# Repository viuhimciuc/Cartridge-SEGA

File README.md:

# 🎮 Cartridge-SEGA: Sega Genesis Cartridge PCBs 🕹️

An open-source collection of hardware design files for **Sega Genesis / Mega Drive** cartridge PCBs (Printed Circuit Boards). Designed from scratch or reverse-engineered using **KiCad**, this repository provides schemas and layouts for creating custom cartridges, multi-game boards, and memory adapters.

---

## 📂 Repository Structure

The project is organized into several key hardware modules:

*   **`GEN-CART-171-6329A-7147A`** — Replica or custom variant of standard Sega Genesis cartridge PCBs.
*   **`GEN-CART-171-6570A`** — Re-engineered files based on the classic 171-6570A board layout.
*   **`GEN-CART-171-6570A_MultiGames`** — Modded version supporting multiple games on a single cartridge via bank switching or custom routing.
*   **`TSOP_Adapter_M29FxxxF`** — A specialized adapter board converting TSOP flash memory chips (like the M29F series) to DIP/SOP layouts suitable for retro console cartridges.

---

## 🛠️ Built With

*   [KiCad EDA](https://www.kicad.org/) — A Cross-Platform and Open Source Electronics Design Automation Suite.

---

## 📸 Gallery & Visuals

### 🔧 Component Placement / PCB Layout Preview

---

## 🚀 Getting Started

### 📋 Prerequisites
To open, edit, or export production files (Gerbers) from this project, you need:
*   **KiCad 7.0 or newer** (Recommended)

### 📥 Cloning the Repository
```bash
git clone https://github.com/viuhimciuc/Cartridge-SEGA.git
```

### ⚙️ How to Generate Gerber Files for Manufacturing
1. Open the `.kicad_pro` project file from any folder in KiCad.
2. Open the **PCB Editor** (`.kicad_pcb`).
3. Go to **File** -> **Fabrication Outputs** -> **Gerbers (.gbr)**.
4. Set your output directory and click **Plot**.
5. Click **Generate Drill Files** to export standard NC drill configurations.
6. Zip all generated files and send them to your preferred PCB manufacturer (e.g., JLCPCB, PCBWay).

---

## 🤝 Contributing

Contributions, bug reports, and hardware improvements are highly welcome! 
1. **Fork** the Project.
2. Create your **Feature Branch** (`git checkout -b feature/AmazingFeature`).
3. **Commit** your Changes (`git commit -m 'Add some AmazingFeature'`).
4. **Push** to the Branch (`git push origin feature/AmazingFeature`).
5. Open a **Pull Request**.

---

## 📄 License

This project is licensed under the MIT License - see the [LICENSE](LICENSE) file for details.

---

<p align="center"> Developed with ❤️ for the Retro Gaming Community </p>

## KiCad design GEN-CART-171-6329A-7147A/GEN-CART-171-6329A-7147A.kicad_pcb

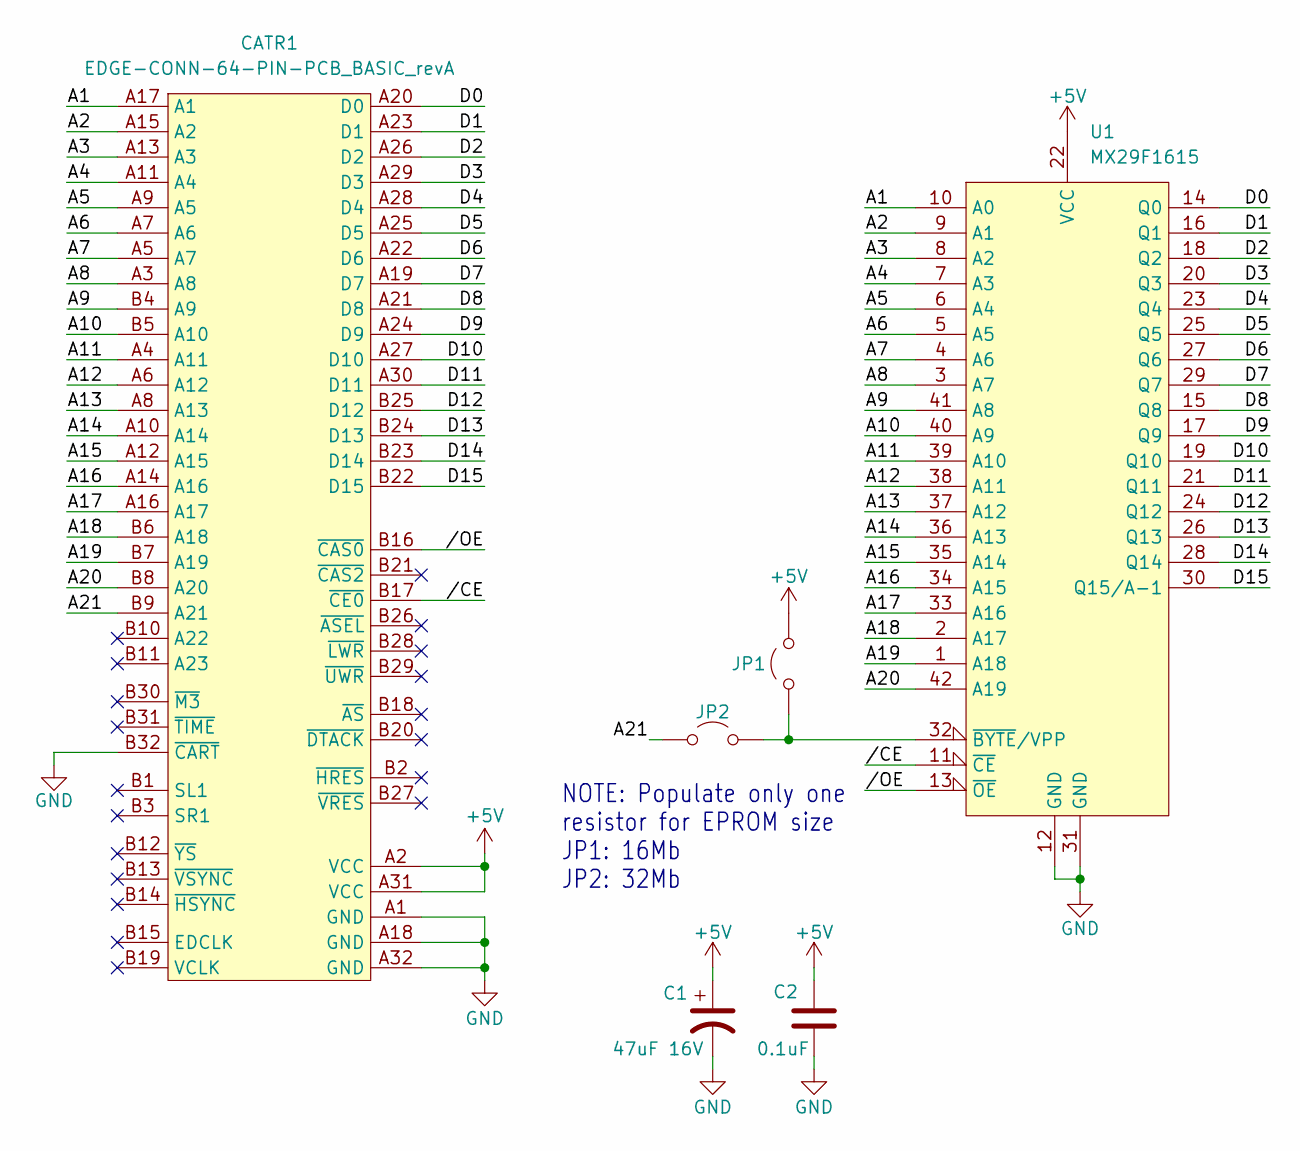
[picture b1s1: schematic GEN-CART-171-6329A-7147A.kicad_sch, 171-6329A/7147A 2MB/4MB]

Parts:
C1: 47uF 16V; CP_Radial_D5.0mm_P2.50mm
C2: 0.1uF; C_Axial_L3.8mm_D2.6mm_P10.00mm_Horizontal
CATR1: EDGE-CONN-64-PIN-PCB_BASIC_revA; PCB_revA-CART-64-2.54-CONN
JP1, JP2: Jumper_2_Open; Jumper_P10.16mm_D0.7mm
U1: MX29F1615; DIP-42_W15.24mm

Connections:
+5V: C1.1, C2.1, CATR1.A2 (VCC), CATR1.A31 (VCC), JP1.2 (B), U1.22 (VCC)
/A1: CATR1.A17 (A1), U1.10 (A0)
/A2: CATR1.A15 (A2), U1.9 (A1)
/A3: CATR1.A13 (A3), U1.8 (A2)
/A4: CATR1.A11 (A4), U1.7 (A3)
/A5: CATR1.A9 (A5), U1.6 (A4)
/A6: CATR1.A7 (A6), U1.5 (A5)
/A7: CATR1.A5 (A7), U1.4 (A6)
/A8: CATR1.A3 (A8), U1.3 (A7)
/A9: CATR1.B4 (A9), U1.41 (A8)
/A10: CATR1.B5 (A10), U1.40 (A9)
/A11: CATR1.A4 (A11), U1.39 (A10)
/A12: CATR1.A6 (A12), U1.38 (A11)
/A13: CATR1.A8 (A13), U1.37 (A12)
/A14: CATR1.A10 (A14), U1.36 (A13)
/A15: CATR1.A12 (A15), U1.35 (A14)
/A16: CATR1.A14 (A16), U1.34 (A15)
/A17: CATR1.A16 (A17), U1.33 (A16)
/A18: CATR1.B6 (A18), U1.2 (A17)
/A19: CATR1.B7 (A19), U1.1 (A18)
/A20: CATR1.B8 (A20), U1.42 (A19)
/A21: CATR1.B9 (A21), JP2.1 (A)
/D0: CATR1.A20 (D0), U1.14 (Q0)
/D1: CATR1.A23 (D1), U1.16 (Q1)
/D2: CATR1.A26 (D2), U1.18 (Q2)
/D3: CATR1.A29 (D3), U1.20 (Q3)
/D4: CATR1.A28 (D4), U1.23 (Q4)
/D5: CATR1.A25 (D5), U1.25 (Q5)
/D6: CATR1.A22 (D6), U1.27 (Q6)
/D7: CATR1.A19 (D7), U1.29 (Q7)
/D8: CATR1.A21 (D8), U1.15 (Q8)
/D9: CATR1.A24 (D9), U1.17 (Q9)
/D10: CATR1.A27 (D10), U1.19 (Q10)
/D11: CATR1.A30 (D11), U1.21 (Q11)
/D12: CATR1.B25 (D12), U1.24 (Q12)
/D13: CATR1.B24 (D13), U1.26 (Q13)
/D14: CATR1.B23 (D14), U1.28 (Q14)
/D15: CATR1.B22 (D15), U1.30 (Q15/A-1)
//CE: CATR1.B17 (~CE0), U1.11 (~CE)
//OE: CATR1.B16 (~CAS0), U1.13 (~OE)
GND: C1.2, C2.2, CATR1.A1 (GND), CATR1.A18 (GND), CATR1.A32 (GND), CATR1.B32 (~CART), U1.12 (GND), U1.31 (GND)
unnamed: JP1.1 (A), JP2.2 (B), U1.32 (~BYTE/VPP)

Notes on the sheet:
NOTE: Populate only one resistor for EPROM size JP1: 16Mb JP2: 32Mb

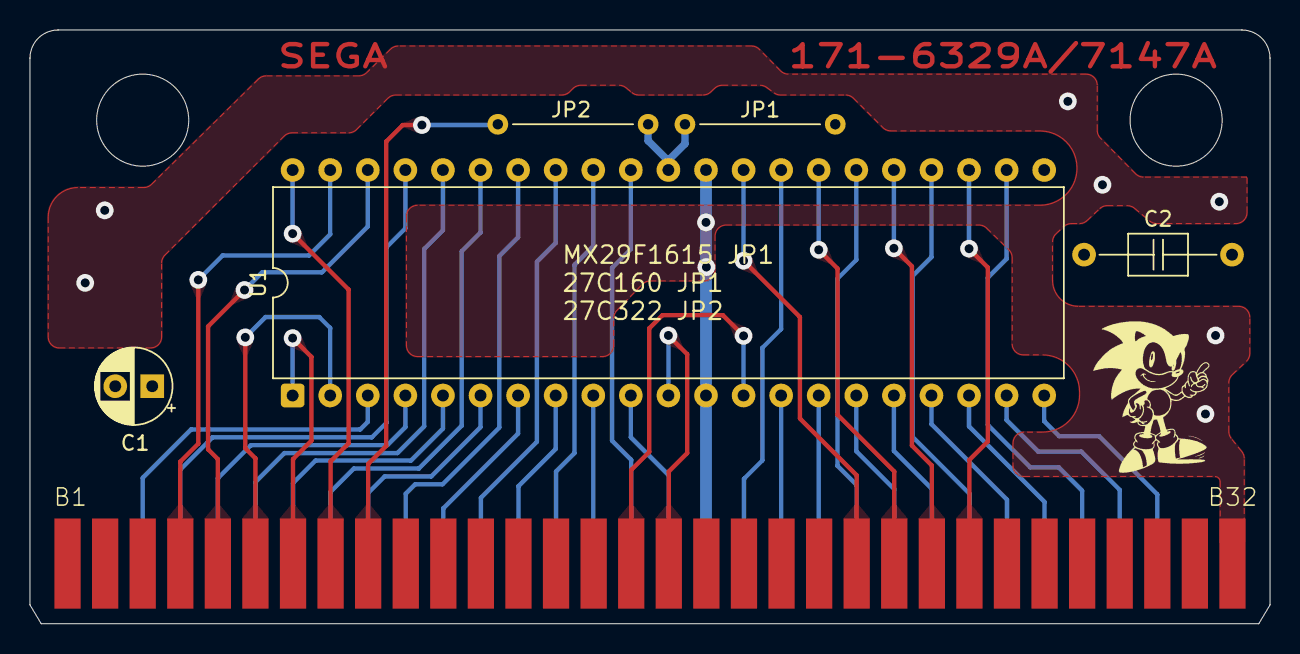
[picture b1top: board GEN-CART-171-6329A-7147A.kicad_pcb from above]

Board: 2 copper layers, 83.8 x 40.1 mm, 6 parts (0 on the bottom side), 42 nets.

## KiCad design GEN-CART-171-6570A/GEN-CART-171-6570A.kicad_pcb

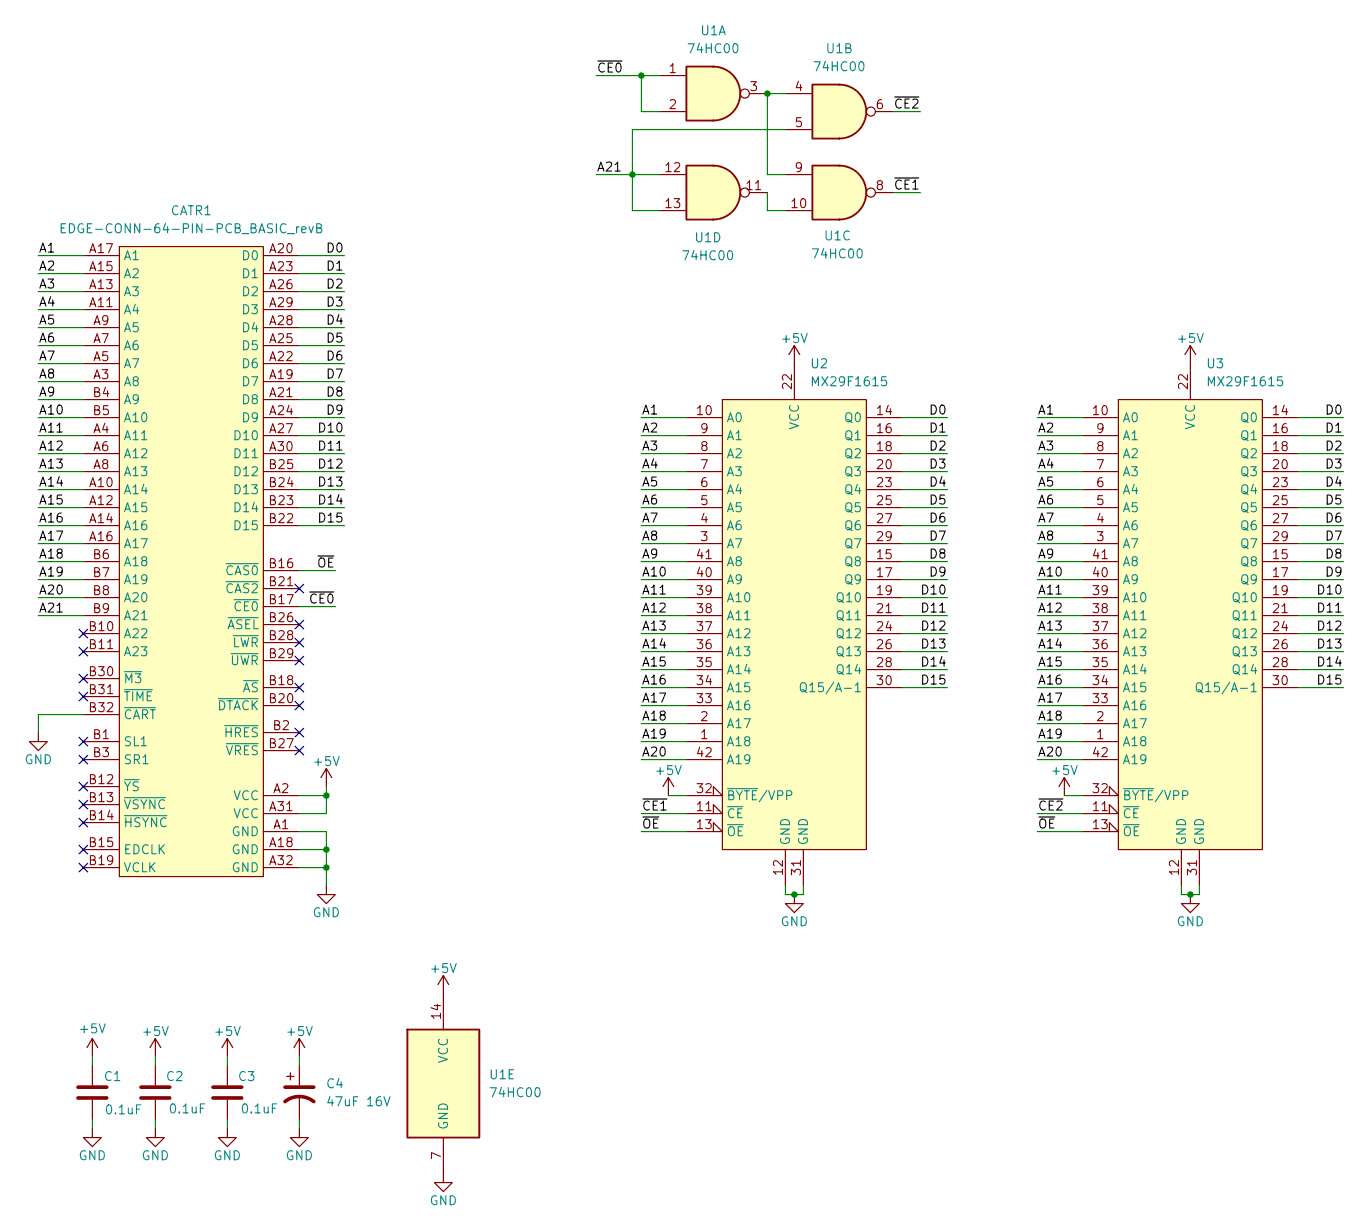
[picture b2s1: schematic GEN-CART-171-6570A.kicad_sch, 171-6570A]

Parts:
C1, C2, C3: 0.1uF; C_Axial_L3.8mm_D2.6mm_P10.00mm_Horizontal
C4: 47uF 16V; CP_Radial_D5.0mm_P2.50mm
CATR1: EDGE-CONN-64-PIN-PCB_BASIC_revB; PCB_revB-CART-64-2.54-CONN
U1: 74HC00; DIP-14_W7.62mm
U2, U3: MX29F1615; DIP-42_W15.24mm

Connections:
+5V: C1.1, C2.1, C3.1, C4.1, CATR1.A2 (VCC), CATR1.A31 (VCC), U1.14 (VCC), U2.22 (VCC), U2.32 (~BYTE/VPP), U3.22 (VCC), U3.32 (~BYTE/VPP)
/A1: CATR1.A17 (A1), U2.10 (A0), U3.10 (A0)
/A2: CATR1.A15 (A2), U2.9 (A1), U3.9 (A1)
/A3: CATR1.A13 (A3), U2.8 (A2), U3.8 (A2)
/A4: CATR1.A11 (A4), U2.7 (A3), U3.7 (A3)
/A5: CATR1.A9 (A5), U2.6 (A4), U3.6 (A4)
/A6: CATR1.A7 (A6), U2.5 (A5), U3.5 (A5)
/A7: CATR1.A5 (A7), U2.4 (A6), U3.4 (A6)
/A8: CATR1.A3 (A8), U2.3 (A7), U3.3 (A7)
/A9: CATR1.B4 (A9), U2.41 (A8), U3.41 (A8)
/A10: CATR1.B5 (A10), U2.40 (A9), U3.40 (A9)
/A11: CATR1.A4 (A11), U2.39 (A10), U3.39 (A10)
/A12: CATR1.A6 (A12), U2.38 (A11), U3.38 (A11)
/A13: CATR1.A8 (A13), U2.37 (A12), U3.37 (A12)
/A14: CATR1.A10 (A14), U2.36 (A13), U3.36 (A13)
/A15: CATR1.A12 (A15), U2.35 (A14), U3.35 (A14)
/A16: CATR1.A14 (A16), U2.34 (A15), U3.34 (A15)
/A17: CATR1.A16 (A17), U2.33 (A16), U3.33 (A16)
/A18: CATR1.B6 (A18), U2.2 (A17), U3.2 (A17)
/A19: CATR1.B7 (A19), U2.1 (A18), U3.1 (A18)
/A20: CATR1.B8 (A20), U2.42 (A19), U3.42 (A19)
/A21: CATR1.B9 (A21), U1.5, U1.12, U1.13
/D0: CATR1.A20 (D0), U2.14 (Q0), U3.14 (Q0)
/D1: CATR1.A23 (D1), U2.16 (Q1), U3.16 (Q1)
/D2: CATR1.A26 (D2), U2.18 (Q2), U3.18 (Q2)
/D3: CATR1.A29 (D3), U2.20 (Q3), U3.20 (Q3)
/D4: CATR1.A28 (D4), U2.23 (Q4), U3.23 (Q4)
/D5: CATR1.A25 (D5), U2.25 (Q5), U3.25 (Q5)
/D6: CATR1.A22 (D6), U2.27 (Q6), U3.27 (Q6)
/D7: CATR1.A19 (D7), U2.29 (Q7), U3.29 (Q7)
/D8: CATR1.A21 (D8), U2.15 (Q8), U3.15 (Q8)
/D9: CATR1.A24 (D9), U2.17 (Q9), U3.17 (Q9)
/D10: CATR1.A27 (D10), U2.19 (Q10), U3.19 (Q10)
/D11: CATR1.A30 (D11), U2.21 (Q11), U3.21 (Q11)
/D12: CATR1.B25 (D12), U2.24 (Q12), U3.24 (Q12)
/D13: CATR1.B24 (D13), U2.26 (Q13), U3.26 (Q13)
/D14: CATR1.B23 (D14), U2.28 (Q14), U3.28 (Q14)
/D15: CATR1.B22 (D15), U2.30 (Q15/A-1), U3.30 (Q15/A-1)
/~CE0: CATR1.B17 (~CE0), U1.1, U1.2
/~CE1: U1.8, U2.11 (~CE)
/~CE2: U1.6, U3.11 (~CE)
/~OE: CATR1.B16 (~CAS0), U2.13 (~OE), U3.13 (~OE)
GND: C1.2, C2.2, C3.2, C4.2, CATR1.A1 (GND), CATR1.A18 (GND), CATR1.A32 (GND), CATR1.B32 (~CART), U1.7 (GND), U2.12 (GND), U2.31 (GND), U3.12 (GND), U3.31 (GND); also elsewhere on the board
unnamed: U1.3, U1.4, U1.9
unnamed: U1.10, U1.11

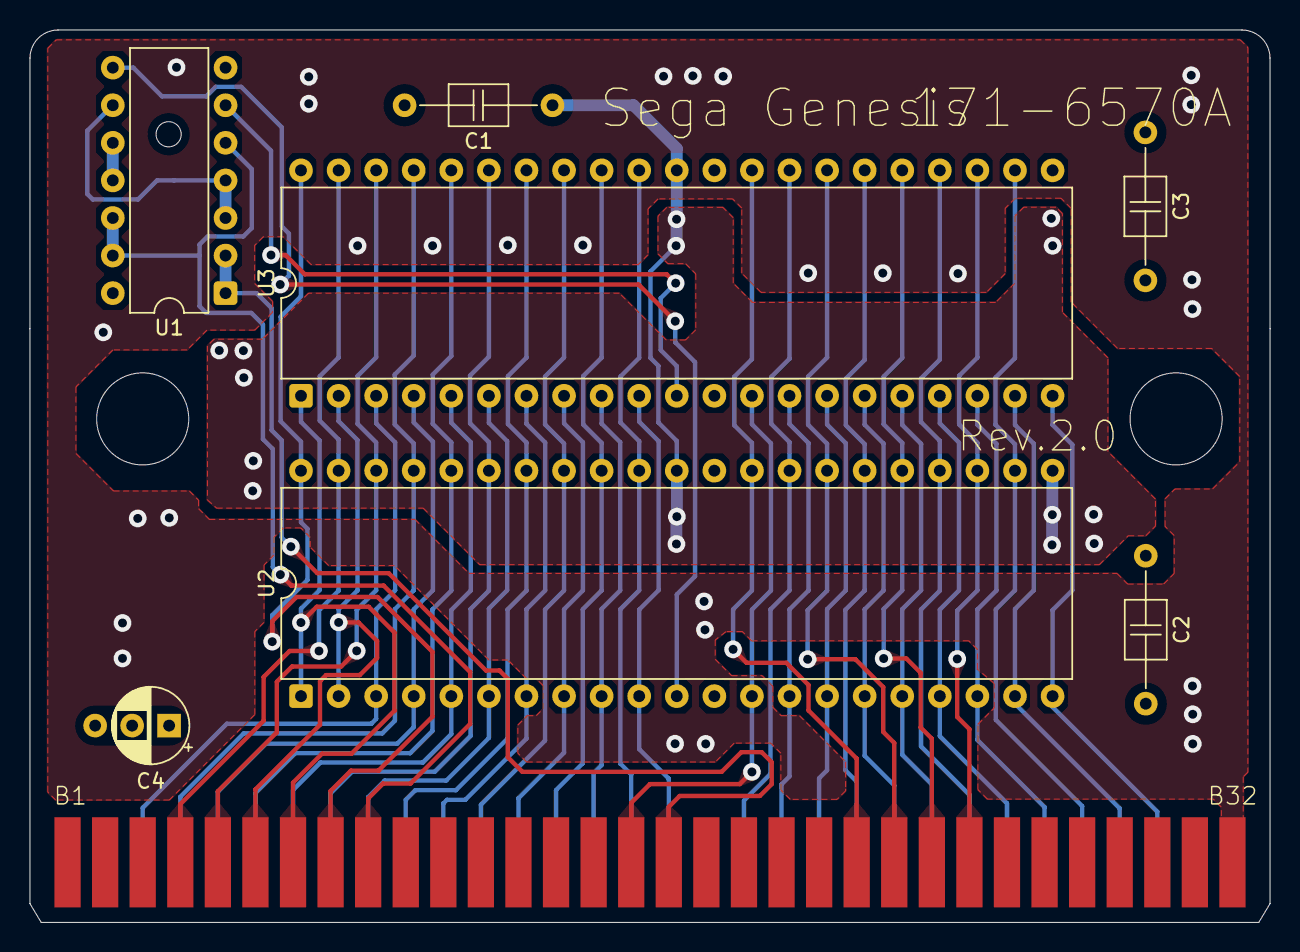
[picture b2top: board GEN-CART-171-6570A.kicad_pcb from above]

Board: 2 copper layers, 83.8 x 60.3 mm, 9 parts (0 on the bottom side), 45 nets.

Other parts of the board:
GND: (no value)

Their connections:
GND: GND.2; also elsewhere on the board

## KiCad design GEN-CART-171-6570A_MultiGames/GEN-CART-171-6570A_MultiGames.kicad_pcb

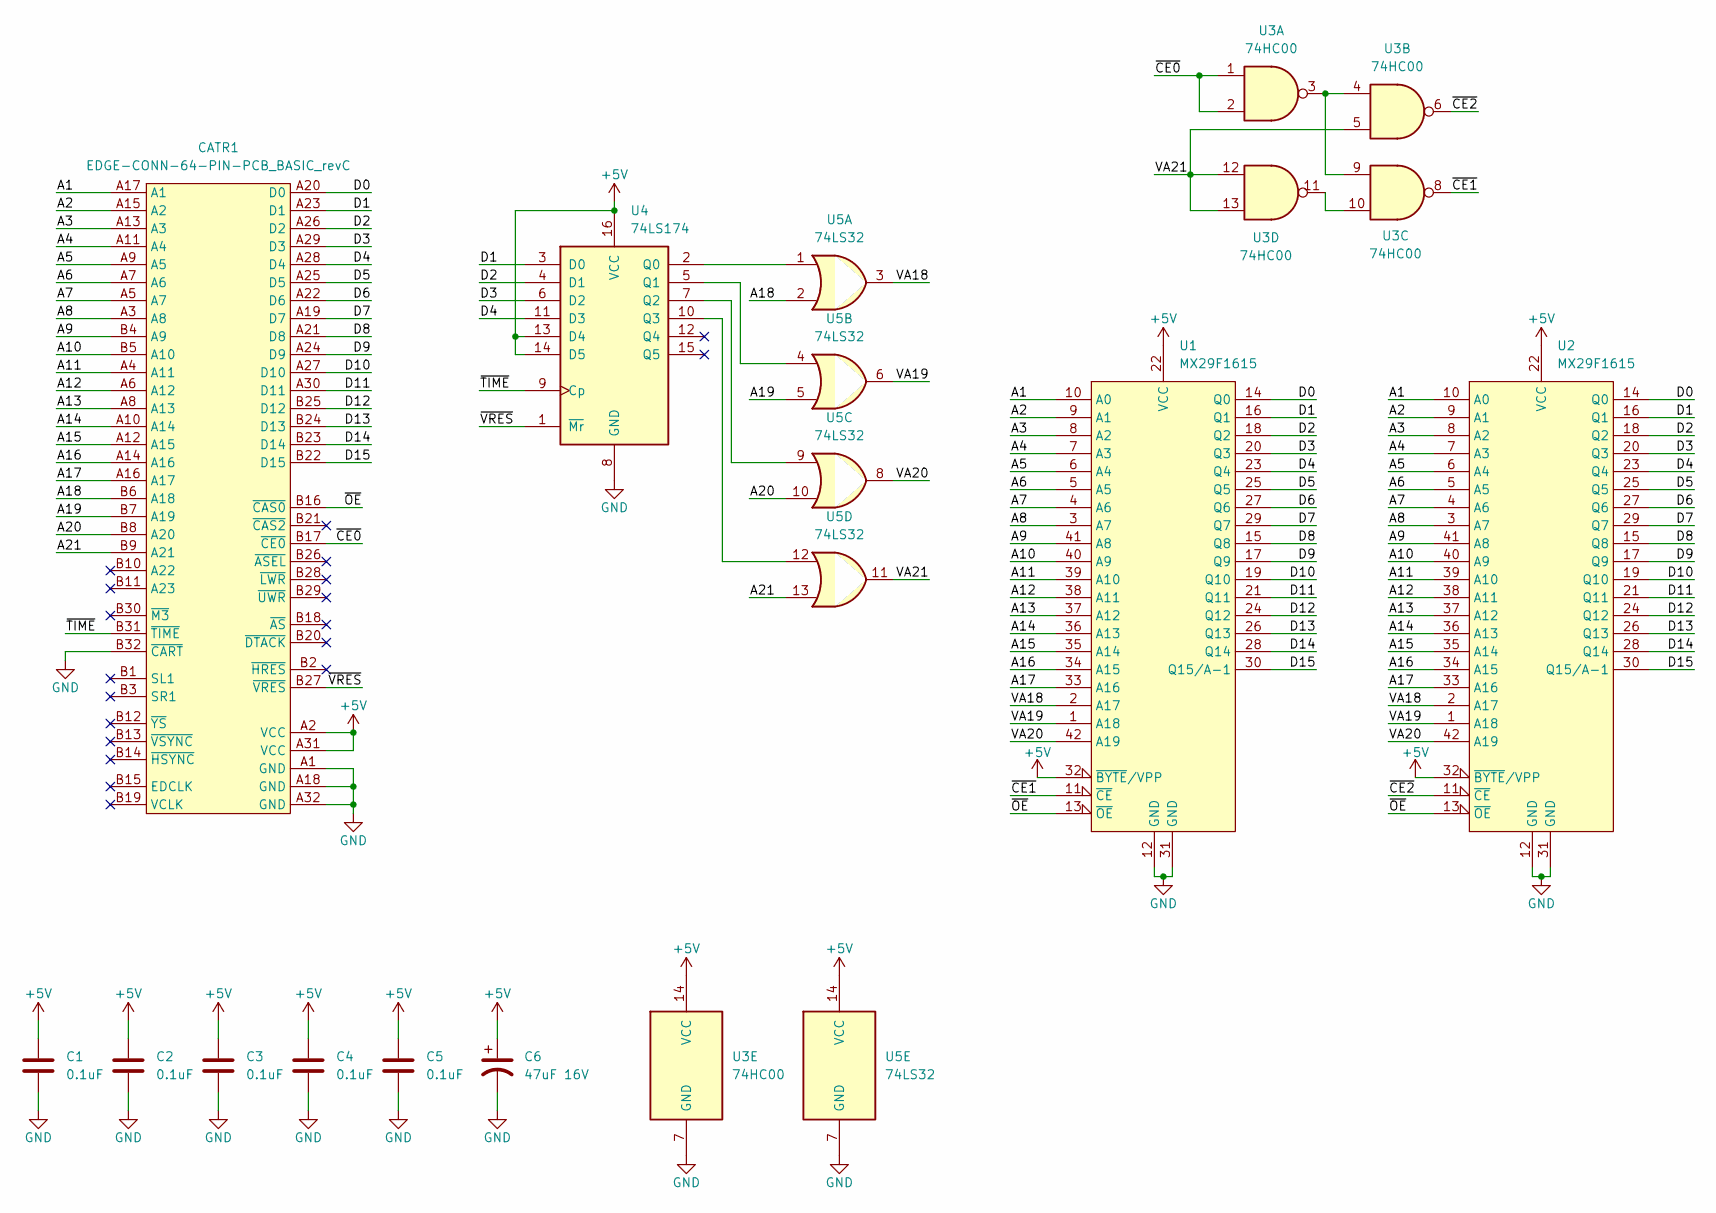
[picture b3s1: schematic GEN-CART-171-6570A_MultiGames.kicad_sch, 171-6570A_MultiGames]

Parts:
C1: 0.1uF; C_Axial_L3.8mm_D2.6mm_P12.50mm_Horizontal
C2, C3: 0.1uF; C_Axial_L3.8mm_D2.6mm_P10.00mm_Horizontal
C4, C5: 0.1uF; C_0805_2012Metric_Pad1.18x1.45mm_HandSolder
C6: 47uF 16V; CP_Radial_D5.0mm_P2.50mm
CATR1: EDGE-CONN-64-PIN-PCB_BASIC_revC; PCB_revC-CART-64-2.54-CONN
U1, U2: MX29F1615; DIP-42_W15.24mm
U3: 74HC00; DIP-14_W7.62mm
U4: 74LS174; SOIC-16_3.9x9.9mm_P1.27mm
U5: 74LS32; SOIC-14_3.9x8.7mm_P1.27mm

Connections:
+5V: C1.1, C2.1, C3.1, C4.1, C5.1, C6.1, CATR1.A2 (VCC), CATR1.A31 (VCC), U1.22 (VCC), U1.32 (~BYTE/VPP), U2.22 (VCC), U2.32 (~BYTE/VPP), U3.14 (VCC), U4.13 (D4), U4.14 (D5), U4.16 (VCC), U5.14 (VCC)
/A1: CATR1.A17 (A1), U1.10 (A0), U2.10 (A0)
/A2: CATR1.A15 (A2), U1.9 (A1), U2.9 (A1)
/A3: CATR1.A13 (A3), U1.8 (A2), U2.8 (A2)
/A4: CATR1.A11 (A4), U1.7 (A3), U2.7 (A3)
/A5: CATR1.A9 (A5), U1.6 (A4), U2.6 (A4)
/A6: CATR1.A7 (A6), U1.5 (A5), U2.5 (A5)
/A7: CATR1.A5 (A7), U1.4 (A6), U2.4 (A6)
/A8: CATR1.A3 (A8), U1.3 (A7), U2.3 (A7)
/A9: CATR1.B4 (A9), U1.41 (A8), U2.41 (A8)
/A10: CATR1.B5 (A10), U1.40 (A9), U2.40 (A9)
/A11: CATR1.A4 (A11), U1.39 (A10), U2.39 (A10)
/A12: CATR1.A6 (A12), U1.38 (A11), U2.38 (A11)
/A13: CATR1.A8 (A13), U1.37 (A12), U2.37 (A12)
/A14: CATR1.A10 (A14), U1.36 (A13), U2.36 (A13)
/A15: CATR1.A12 (A15), U1.35 (A14), U2.35 (A14)
/A16: CATR1.A14 (A16), U1.34 (A15), U2.34 (A15)
/A17: CATR1.A16 (A17), U1.33 (A16), U2.33 (A16)
/A18: CATR1.B6 (A18), U5.2
/A19: CATR1.B7 (A19), U5.5
/A20: CATR1.B8 (A20), U5.10
/A21: CATR1.B9 (A21), U5.13
/D0: CATR1.A20 (D0), U1.14 (Q0), U2.14 (Q0)
/D1: CATR1.A23 (D1), U1.16 (Q1), U2.16 (Q1), U4.3 (D0)
/D2: CATR1.A26 (D2), U1.18 (Q2), U2.18 (Q2), U4.4 (D1)
/D3: CATR1.A29 (D3), U1.20 (Q3), U2.20 (Q3), U4.6 (D2)
/D4: CATR1.A28 (D4), U1.23 (Q4), U2.23 (Q4), U4.11 (D3)
/D5: CATR1.A25 (D5), U1.25 (Q5), U2.25 (Q5)
/D6: CATR1.A22 (D6), U1.27 (Q6), U2.27 (Q6)
/D7: CATR1.A19 (D7), U1.29 (Q7), U2.29 (Q7)
/D8: CATR1.A21 (D8), U1.15 (Q8), U2.15 (Q8)
/D9: CATR1.A24 (D9), U1.17 (Q9), U2.17 (Q9)
/D10: CATR1.A27 (D10), U1.19 (Q10), U2.19 (Q10)
/D11: CATR1.A30 (D11), U1.21 (Q11), U2.21 (Q11)
/D12: CATR1.B25 (D12), U1.24 (Q12), U2.24 (Q12)
/D13: CATR1.B24 (D13), U1.26 (Q13), U2.26 (Q13)
/D14: CATR1.B23 (D14), U1.28 (Q14), U2.28 (Q14)
/D15: CATR1.B22 (D15), U1.30 (Q15/A-1), U2.30 (Q15/A-1)
/VA18: U1.2 (A17), U2.2 (A17), U5.3
/VA19: U1.1 (A18), U2.1 (A18), U5.6
/VA20: U1.42 (A19), U2.42 (A19), U5.8
/VA21: U3.5, U3.12, U3.13, U5.11
/~CE0: CATR1.B17 (~CE0), U3.1, U3.2
/~CE1: U1.11 (~CE), U3.8
/~CE2: U2.11 (~CE), U3.6
/~OE: CATR1.B16 (~CAS0), U1.13 (~OE), U2.13 (~OE)
/~TIME: CATR1.B31 (~TIME), U4.9 (Cp)
/~VRES: CATR1.B27 (~VRES), U4.1 (~Mr)
GND: C1.2, C2.2, C3.2, C4.2, C5.2, C6.2, CATR1.A1 (GND), CATR1.A18 (GND), CATR1.A32 (GND), CATR1.B32 (~CART), U1.12 (GND), U1.31 (GND), U2.12 (GND), U2.31 (GND), U3.7 (GND), U4.8 (GND), U5.7 (GND)
unnamed: U3.3, U3.4, U3.9
unnamed: U3.10, U3.11
unnamed: U4.2 (Q0), U5.1
unnamed: U4.5 (Q1), U5.4
unnamed: U4.7 (Q2), U5.9
unnamed: U4.10 (Q3), U5.12

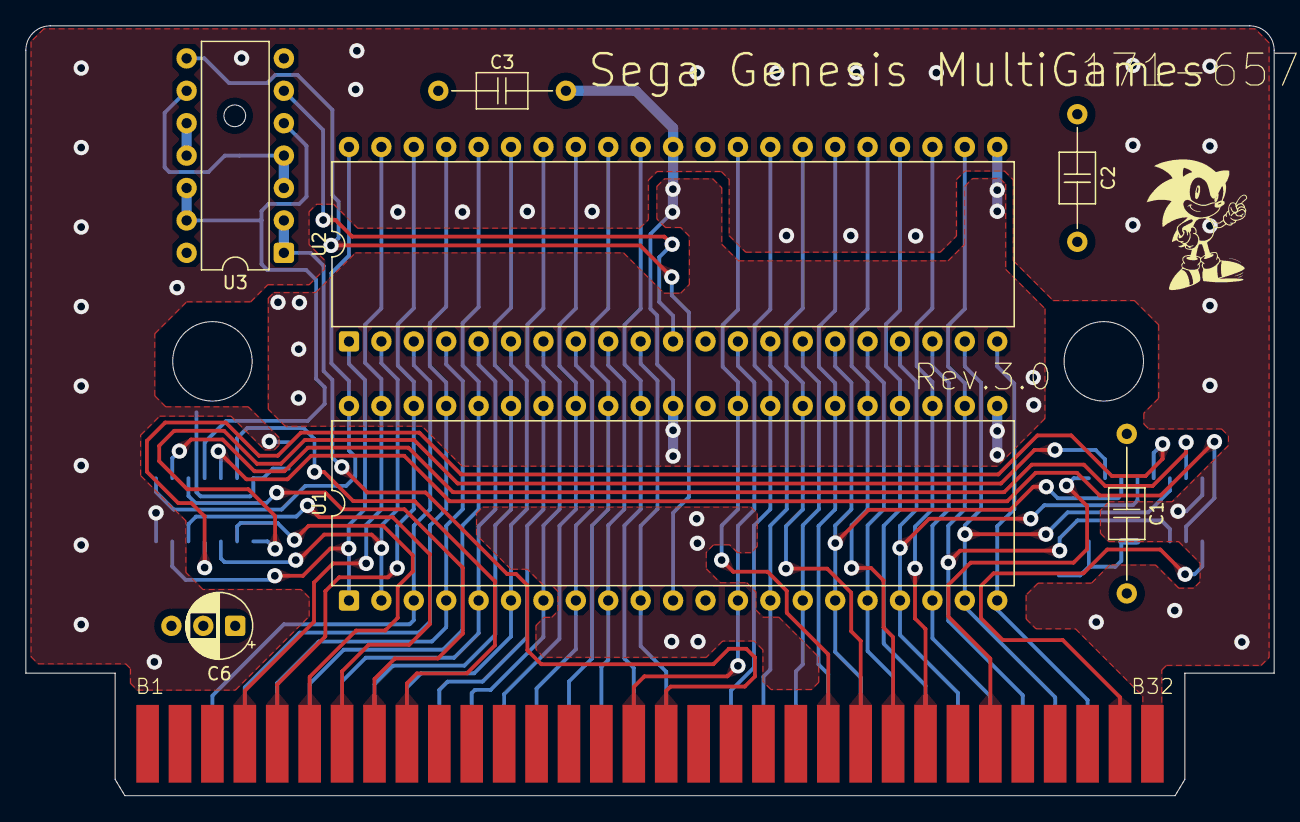
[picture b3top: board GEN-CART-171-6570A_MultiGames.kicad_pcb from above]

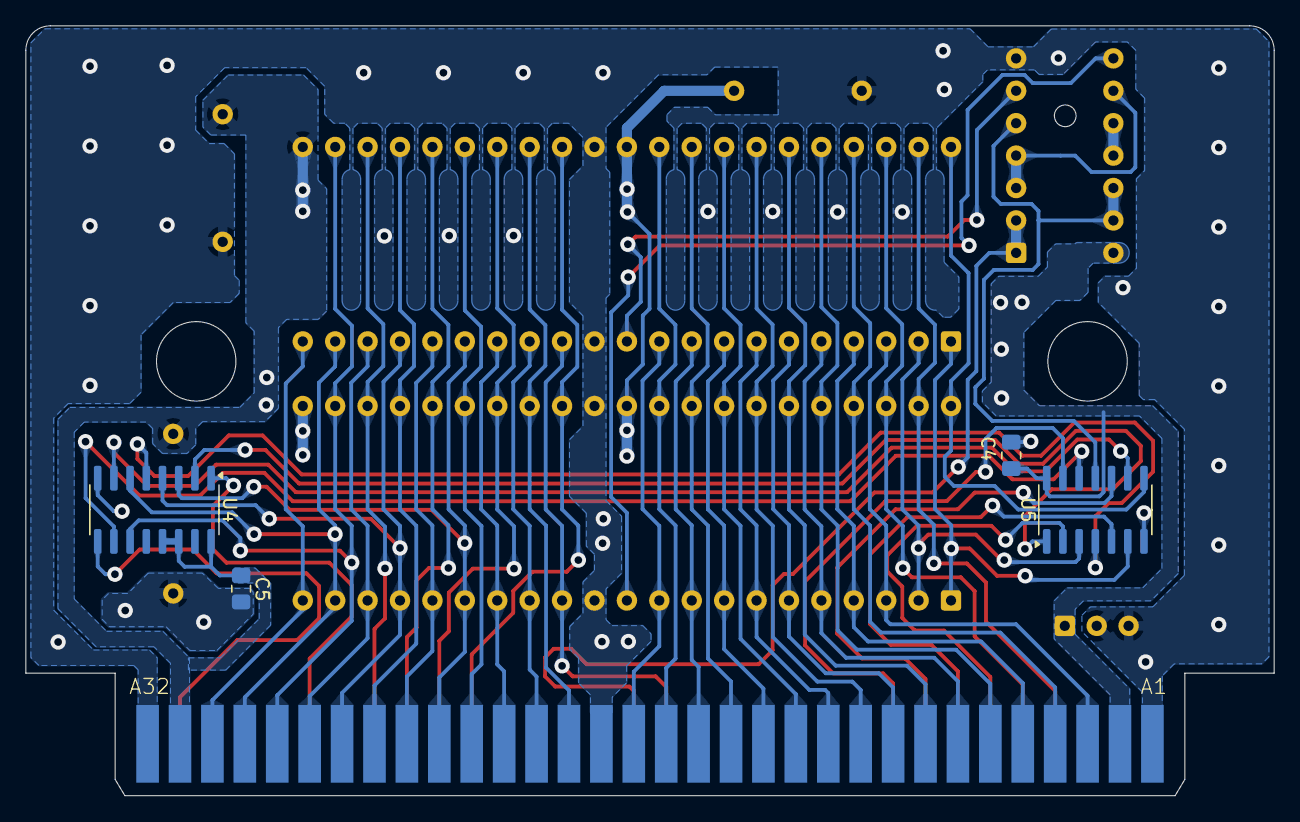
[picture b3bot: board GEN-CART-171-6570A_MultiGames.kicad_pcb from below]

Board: 2 copper layers, 97.8 x 60.3 mm, 12 parts (4 on the bottom side), 55 nets.

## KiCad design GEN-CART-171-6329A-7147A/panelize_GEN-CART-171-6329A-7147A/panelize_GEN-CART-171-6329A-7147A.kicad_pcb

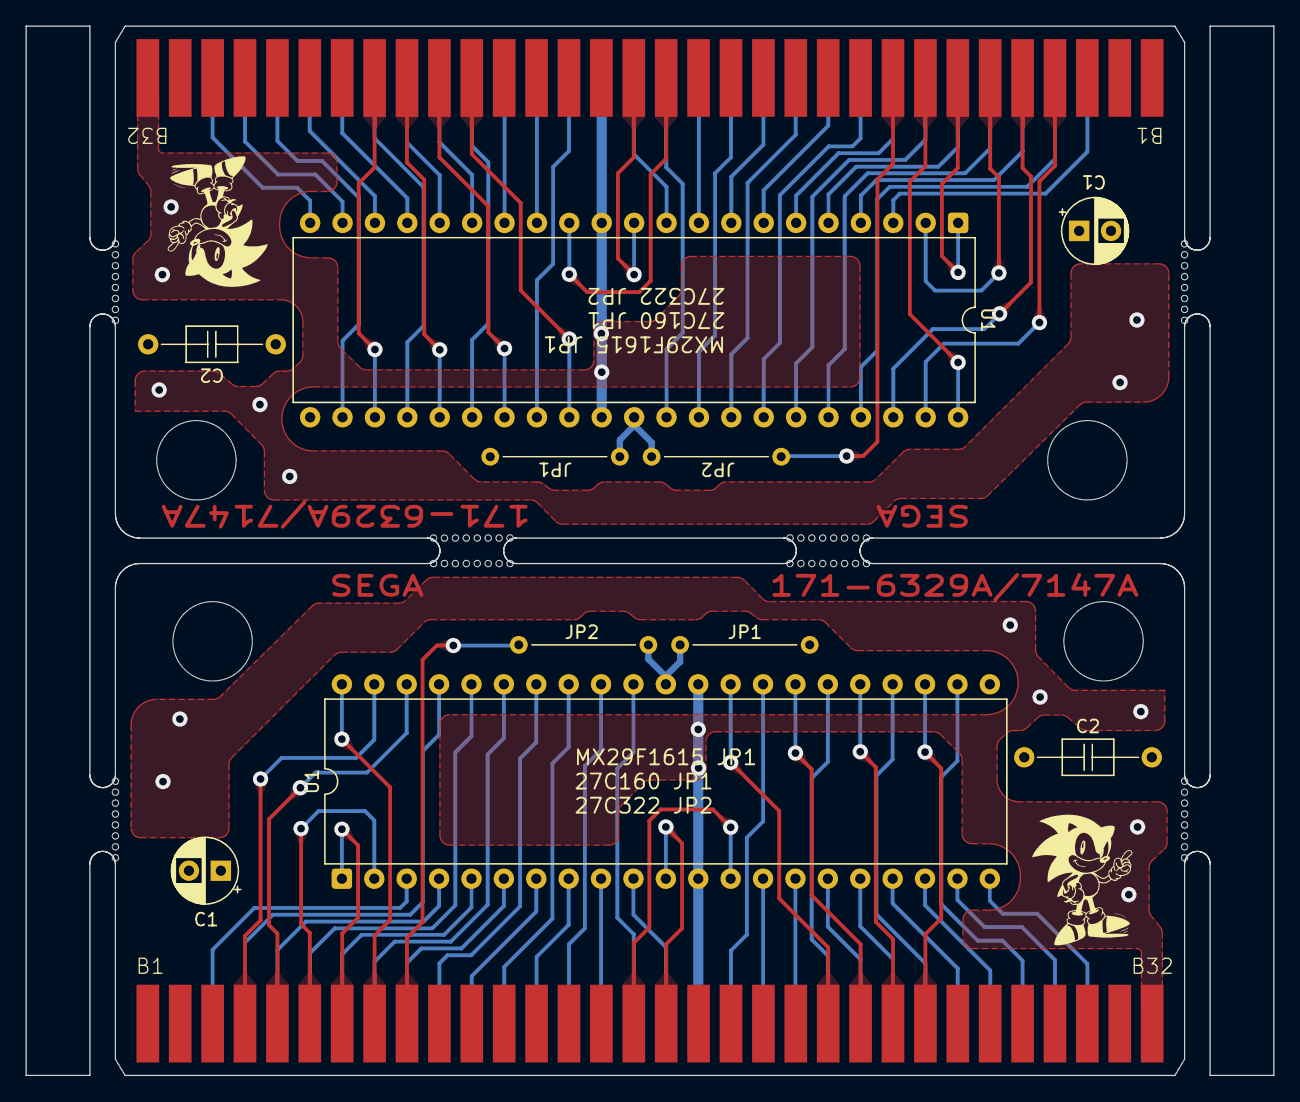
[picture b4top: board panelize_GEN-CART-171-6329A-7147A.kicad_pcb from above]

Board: 2 copper layers, 97.8 x 82.3 mm, 76 parts (0 on the bottom side), 84 nets.

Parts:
C1, C1#2: 47uF 16V; CP_Radial_D5.0mm_P2.50mm
C2, C2#2: 0.1uF; C_Axial_L3.8mm_D2.6mm_P10.00mm_Horizontal
CATR1, CATR1#2: EDGE-CONN-64-PIN-PCB_BASIC_revA; PCB_revA-CART-64-2.54-CONN
JP1, JP1#2, JP2, JP2#2: Jumper_2_Open; Jumper_P10.16mm_D0.7mm
KiKit_MB_1_1, KiKit_MB_1_2, KiKit_MB_1_3, KiKit_MB_1_4, KiKit_MB_1_5, KiKit_MB_1_6, KiKit_MB_1_7, KiKit_MB_1_8, KiKit_MB_2_1, KiKit_MB_2_2, KiKit_MB_2_3, KiKit_MB_2_4, KiKit_MB_2_5, KiKit_MB_2_6, KiKit_MB_2_7, KiKit_MB_2_8, KiKit_MB_3_1, KiKit_MB_3_2, KiKit_MB_3_3, KiKit_MB_3_4, KiKit_MB_3_5, KiKit_MB_3_6, KiKit_MB_3_7, KiKit_MB_3_8, KiKit_MB_4_1, KiKit_MB_4_2, KiKit_MB_4_3, KiKit_MB_4_4, KiKit_MB_4_5, KiKit_MB_4_6, KiKit_MB_4_7, KiKit_MB_4_8, KiKit_MB_5_1, KiKit_MB_5_2, KiKit_MB_5_3, KiKit_MB_5_4, KiKit_MB_5_5, KiKit_MB_5_6, KiKit_MB_5_7, KiKit_MB_5_8, KiKit_MB_6_1, KiKit_MB_6_2, KiKit_MB_6_3, KiKit_MB_6_4, KiKit_MB_6_5, KiKit_MB_6_6, KiKit_MB_6_7, KiKit_MB_6_8, KiKit_MB_7_1, KiKit_MB_7_2, KiKit_MB_7_3, KiKit_MB_7_4, KiKit_MB_7_5, KiKit_MB_7_6, KiKit_MB_7_7, KiKit_MB_7_8, KiKit_MB_8_1, KiKit_MB_8_2, KiKit_MB_8_3, KiKit_MB_8_4, KiKit_MB_8_5, KiKit_MB_8_6, KiKit_MB_8_7, KiKit_MB_8_8: NPTH
U1, U1#2: MX29F1615; DIP-42_W15.24mm

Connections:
Board_0-+5V: C1#2.1, C2.1, CATR1#2.A2 (VCC), CATR1#2.A31 (VCC), JP1.2 (B), U1#2.22 (VCC)
Board_0-/A1: CATR1#2.A17 (A1), U1#2.10 (A0)
Board_0-/A2: CATR1#2.A15 (A2), U1#2.9 (A1)
Board_0-/A3: CATR1#2.A13 (A3), U1#2.8 (A2)
Board_0-/A4: CATR1#2.A11 (A4), U1#2.7 (A3)
Board_0-/A5: CATR1#2.A9 (A5), U1#2.6 (A4)
Board_0-/A6: CATR1#2.A7 (A6), U1#2.5 (A5)
Board_0-/A7: CATR1#2.A5 (A7), U1#2.4 (A6)
Board_0-/A8: CATR1#2.A3 (A8), U1#2.3 (A7)
Board_0-/A9: CATR1#2.B4 (A9), U1#2.41 (A8)
Board_0-/A10: CATR1#2.B5 (A10), U1#2.40 (A9)
Board_0-/A11: CATR1#2.A4 (A11), U1#2.39 (A10)
Board_0-/A12: CATR1#2.A6 (A12), U1#2.38 (A11)
Board_0-/A13: CATR1#2.A8 (A13), U1#2.37 (A12)
Board_0-/A14: CATR1#2.A10 (A14), U1#2.36 (A13)
Board_0-/A15: CATR1#2.A12 (A15), U1#2.35 (A14)
Board_0-/A16: CATR1#2.A14 (A16), U1#2.34 (A15)
Board_0-/A17: CATR1#2.A16 (A17), U1#2.33 (A16)
Board_0-/A18: CATR1#2.B6 (A18), U1#2.2 (A17)
Board_0-/A19: CATR1#2.B7 (A19), U1#2.1 (A18)
Board_0-/A20: CATR1#2.B8 (A20), U1#2.42 (A19)
Board_0-/A21: CATR1#2.B9 (A21), JP2#2.1 (A)
Board_0-/D0: CATR1#2.A20 (D0), U1#2.14 (Q0)
Board_0-/D1: CATR1#2.A23 (D1), U1#2.16 (Q1)
Board_0-/D2: CATR1#2.A26 (D2), U1#2.18 (Q2)
Board_0-/D3: CATR1#2.A29 (D3), U1#2.20 (Q3)
Board_0-/D4: CATR1#2.A28 (D4), U1#2.23 (Q4)
Board_0-/D5: CATR1#2.A25 (D5), U1#2.25 (Q5)
Board_0-/D6: CATR1#2.A22 (D6), U1#2.27 (Q6)
Board_0-/D7: CATR1#2.A19 (D7), U1#2.29 (Q7)
Board_0-/D8: CATR1#2.A21 (D8), U1#2.15 (Q8)
Board_0-/D9: CATR1#2.A24 (D9), U1#2.17 (Q9)
Board_0-/D10: CATR1#2.A27 (D10), U1#2.19 (Q10)
Board_0-/D11: CATR1#2.A30 (D11), U1#2.21 (Q11)
Board_0-/D12: CATR1#2.B25 (D12), U1#2.24 (Q12)
Board_0-/D13: CATR1#2.B24 (D13), U1#2.26 (Q13)
Board_0-/D14: CATR1#2.B23 (D14), U1#2.28 (Q14)
Board_0-/D15: CATR1#2.B22 (D15), U1#2.30 (Q15/A-1)
Board_0-//CE: CATR1#2.B17 (~CE0), U1#2.11 (~CE)
Board_0-//OE: CATR1#2.B16 (~CAS0), U1#2.13 (~OE)
Board_0-GND: C1#2.2, C2.2, CATR1#2.A1 (GND), CATR1#2.A18 (GND), CATR1#2.A32 (GND), CATR1#2.B32 (~CART), U1#2.12 (GND), U1#2.31 (GND)
Board_0-Net-(JP1-A): JP1.1 (A), JP2#2.2 (B), U1#2.32 (~BYTE/VPP)
Board_1-+5V: C1.1, C2#2.1, CATR1.A2 (VCC), CATR1.A31 (VCC), JP1#2.2 (B), U1.22 (VCC)
Board_1-/A1: CATR1.A17 (A1), U1.10 (A0)
Board_1-/A2: CATR1.A15 (A2), U1.9 (A1)
Board_1-/A3: CATR1.A13 (A3), U1.8 (A2)
Board_1-/A4: CATR1.A11 (A4), U1.7 (A3)
Board_1-/A5: CATR1.A9 (A5), U1.6 (A4)
Board_1-/A6: CATR1.A7 (A6), U1.5 (A5)
Board_1-/A7: CATR1.A5 (A7), U1.4 (A6)
Board_1-/A8: CATR1.A3 (A8), U1.3 (A7)
Board_1-/A9: CATR1.B4 (A9), U1.41 (A8)
Board_1-/A10: CATR1.B5 (A10), U1.40 (A9)
Board_1-/A11: CATR1.A4 (A11), U1.39 (A10)
Board_1-/A12: CATR1.A6 (A12), U1.38 (A11)
Board_1-/A13: CATR1.A8 (A13), U1.37 (A12)
Board_1-/A14: CATR1.A10 (A14), U1.36 (A13)
Board_1-/A15: CATR1.A12 (A15), U1.35 (A14)
Board_1-/A16: CATR1.A14 (A16), U1.34 (A15)
Board_1-/A17: CATR1.A16 (A17), U1.33 (A16)
Board_1-/A18: CATR1.B6 (A18), U1.2 (A17)
Board_1-/A19: CATR1.B7 (A19), U1.1 (A18)
Board_1-/A20: CATR1.B8 (A20), U1.42 (A19)
Board_1-/A21: CATR1.B9 (A21), JP2.1 (A)
Board_1-/D0: CATR1.A20 (D0), U1.14 (Q0)
Board_1-/D1: CATR1.A23 (D1), U1.16 (Q1)
Board_1-/D2: CATR1.A26 (D2), U1.18 (Q2)
Board_1-/D3: CATR1.A29 (D3), U1.20 (Q3)
Board_1-/D4: CATR1.A28 (D4), U1.23 (Q4)
Board_1-/D5: CATR1.A25 (D5), U1.25 (Q5)
Board_1-/D6: CATR1.A22 (D6), U1.27 (Q6)
Board_1-/D7: CATR1.A19 (D7), U1.29 (Q7)
Board_1-/D8: CATR1.A21 (D8), U1.15 (Q8)
Board_1-/D9: CATR1.A24 (D9), U1.17 (Q9)
Board_1-/D10: CATR1.A27 (D10), U1.19 (Q10)
Board_1-/D11: CATR1.A30 (D11), U1.21 (Q11)
Board_1-/D12: CATR1.B25 (D12), U1.24 (Q12)
Board_1-/D13: CATR1.B24 (D13), U1.26 (Q13)
Board_1-/D14: CATR1.B23 (D14), U1.28 (Q14)
Board_1-/D15: CATR1.B22 (D15), U1.30 (Q15/A-1)
Board_1-//CE: CATR1.B17 (~CE0), U1.11 (~CE)
Board_1-//OE: CATR1.B16 (~CAS0), U1.13 (~OE)
Board_1-GND: C1.2, C2#2.2, CATR1.A1 (GND), CATR1.A18 (GND), CATR1.A32 (GND), CATR1.B32 (~CART), U1.12 (GND), U1.31 (GND)
Board_1-Net-(JP1-A): JP1#2.1 (A), JP2.2 (B), U1.32 (~BYTE/VPP)
